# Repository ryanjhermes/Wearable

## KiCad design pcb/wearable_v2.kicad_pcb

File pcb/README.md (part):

# pcb — Wearable V2 schematic

KiCad project for the custom ESP32-C3 fab PCB. Open `wearable_v2.kicad_pro` in KiCad 10.

**This is the single living status document for the PCB. There are no dated handoff files.**
Read `## Current state`, `## Verified log` and `## Next actions` below; read the rest only if the
task needs it. `parts/V2_BOM.md` owns part rationale and approval status;
`bom_from_schematic.csv` owns reference designators and quantities.

**Update discipline:** documentation follows saved artifact changes; it does not predict them.
After changing and saving an artifact, run the required verification and immediately update this
file with the observed result and truthful next action. Never defer that update to the end of a
session.

## SETTLED — do not re-verify, do not re-open

Everything in this section is closed. A fresh agent must **not** re-run these checks, re-search these
parts, or re-litigate these decisions. Re-open an item only if the user asks, or if a design object it
depends on actually changes — and say which object changed before you do.

**Design checks — all pass, all current as of 2026-09-18.** The last design change was R10
270k -> 249k on 2026-09-18; ERC, DRC, schematic parity and `analyze_pcb.py` were all re-run after it
and returned results identical to the accepted 2026-09-17 baseline.

| Check | Accepted result | Do not re-run unless |
|---|---|---|
| `sch erc` | 2 violations = the 2 known `pin_to_pin` warnings | the schematic changes |
| `pcb drc` | 5 violations = the known-acceptable set, 0 unconnected | the board changes |
| `pcb drc --schematic-parity` | 0 parity issues, 0 unconnected | either design file changes |
| `analyze_pcb.py` | 51 findings: 2 error / 18 warning / 31 info, all reviewed and accepted | the board changes |
| Visual route + 3D review | Accepted for the first prototype | the board changes |
| CAD mechanical review | PASS for fabrication-file preparation; enclosure rebuilt 2026-09-18 | the board outline or battery envelope changes |
| Fabrication artifact validation | 15/15 PASS | the BOM, board or exports change |

**KiCad F8 (Update PCB from Schematic): do not run it.** The netlist has not changed since parity
last returned 0. KiCad 10.0.5 reintroduces a stale U4 pad net in this project when F8 runs. The
2026-09-18 R10 change was applied by patching the value/MPN/LCSC property fields in both files
directly, precisely to avoid this.

**Battery — CLOSED, final, by user decision 2026-09-18.** The EEMB `LP502030-PCM` already in the
user's possession is the cell for v2. EEMB's own LP502030 specification states a 250 mA maximum
charge current, so the planned 100 mA (0.4 C) is inside rating. **Do not search for alternative
cells, do not price-compare, do not re-open the envelope or wire-count questions.** Alternatives
investigated on 2026-09-17/18 are recorded in the log below for history only.

**JLCPCB — the decisions below are made. Do not re-derive, re-search or re-price them.**

| Settled | Value |
|---|---|
| Service | Standard PCBA |
| Layers / thickness | 4 layers, 1.0 mm |
| Panelization | Panel by JLCPCB, 5 mm process rails |
| Fiducials | Factory-added on the panel. **Do not add local board fiducials** unless JLCPCB actually rejects this workflow |
| Assembly sides | Top and bottom (45 top / 6 bottom) |
| Excluded from placement | BT1 and TP1-TP12 |
| R10 assembly class | `C11425` is Extended. So was the outgoing `C25770`. **No Basic 0402 1% part exists at either value** — checked 2026-09-18, does not need rechecking |
| Substitutions | Not acceptable for regulators, MOSFETs or connectors |
| Gerber/drill ZIP | Current and correct. R10's value lives only on F.Fab, which is not in the gerber set, so the 2026-09-18 change did not alter it |

**What genuinely still requires the live JLCPCB cart — once, not repeatedly.** These are not
desk-checkable and no amount of re-reading this repo will close them. They are the *only* JLCPCB work
left: confirm 4-layer/1.0 mm availability; run the cart's DFM; confirm the factory rails, fiducials
and tooling holes serve both assembly sides; read current stock, lifecycle, assembly class and price;
and eyeball the BOM/CPL overlay, especially J1, U1, U6, U7, U8, U10 and R10. Record the result once,
in the log below, and then treat it as settled too.

**Nothing here is fabrication approval.** Layout complete, checks clean, and artifacts validated are
all separate from reviewed, and all separate from ordered. No order is authorized.

## Current state — 2026-09-18

**The design is complete, internally consistent and fully verified on desk. It has never been built,
measured or ordered.**

*Schematic.* Captured, ERC-clean (2 understood warnings), frozen. One user-approved change since the
2026-09-16 freeze: R10 270k -> 249k on 2026-09-18, a value/MPN/LCSC change only — the netlist is
untouched.

*Layout.* 662 segments, 53 vias, 4 layers. Both inner GND zones filled and saved; In1.Cu carries no
traces and In2.Cu only the approved four 3V3 and two VSYS segments. Project-aware DRC without
refilling gives the 5 known-acceptable warnings, 0 unconnected items and 0 footprint errors; parity
gives 0 issues. `analyze_pcb.py` gives 51 reviewed and accepted findings. Route reviewed visually and
in 3D and accepted for the first prototype.

*Enclosure.* Rebuilt on 2026-09-18 after three structural defects were found in the 2026-09-17/18
geometry (see the log). The board is now mechanically captured: it sits on a 1.25 mm perimeter ledge
in the tray with 1.00 mm of bearing, is held down by full-length lid blocks on both long edges with a
0.05 mm nominal gap, and has 0.25 mm of lateral slop per side instead of 0.50. The halves join on a
continuous 2.445 mm lap joint whose four snap fingers are rooted in the lid wall over their full
6.0 x 0.7 mm section. Closed exterior is now **27.7 x 49.7 x 12.75 mm**. CAD review passes with zero
modeled hard collisions, 2.1 mm battery-to-antenna clearance, a single-piece USB mouth, separate
MAX30101 optical-gasket and TMP117 soft-thermal-pad volumes, and an unobstructed SHT40 vent.

*Power.* Desk power/thermal analysis and an ngspice simulation of the 4V7 boost are complete and give
a conditional pass. The worst-case 4V7 low corner is 4.770 V against the MAX30101's 4.5 V green
minimum, and a green LED pulse moves the rail only 4 mV, so boost dynamics are not a risk. **Two
firmware constraints carry into bring-up: cap BLE TX at 0 dBm, and hold `PPG_PWR_EN` low until 1V8 is
up.** The 3.45 V deep-sleep threshold is provisional pending a measured cell-sag figure.

*Battery.* **Closed and final.** EEMB LP502030-PCM already in hand; its 250 mA maximum charge rating
covers the planned 100 mA. Not to be re-sourced.

*Fabrication package.* `pcb/fabrication/jlcpcb_standard_pcba/` — gerbers, separate PTH/NPTH drills,
the authoritative 25-line/51-part BOM, 45-part top CPL, 6-part bottom CPL, PCB STEP and assembly
review artifacts. Regenerated after the R10 change; `artifact_validation.json` is 15/15 PASS.

*What is left.* Three things, all of which need hardware or the live cart, none of which can be
closed by further desk work: **the JLCPCB cart pass, printing and fit-testing the enclosure, and
bench-validating the rails on the first article.** See the SETTLED section above for what must not be
re-checked, and `## Verification NOT done` for the full list of what genuinely remains.

**Not bench-validated. Not peer-reviewed by a second person. Not approved for fabrication. No order
is authorized.**

## Verified log — append-only

Rows are chronological and **never edited or deleted**, so superseded rows remain visible. Two rows
below are superseded and must not be acted on: the `enclosure` row marked **BLOCKED** (superseded the
same day by the passing CAD mechanical review) and the `battery` row reporting a three-conductor
30 x 20 x 4 mm cell (superseded by the confirmed EEMB `LP502030-PCM` evidence, then closed entirely on
2026-09-18). Where a row conflicts with the SETTLED section or Current state above, those win.

Append one row per accepted check. Never edit or delete a row except to remove obsolete workflow
metadata such as revision fingerprints. A superseded result remains as historical evidence.

| Date | Artifact | Check | Result |
|---|---|---|---|
| 2026-09-16 | schematic | `kicad-cli sch erc` | 0 errors, 2 understood U9 strap warnings |
| 2026-09-16 | schematic | Hand netlist review, net by net | 3 silent opens found and fixed; no others |
| 2026-09-16 | schematic | BOM reconcile vs `parts/V2_BOM.md` | 25 lines / 51 populated, every qty matches |
| 2026-09-16 | schematic | IC pinouts vs local datasheets | 12/12 pin maps, **0 errors** |
| 2026-09-16 | schematic | Footprint courtyards | all 16 enclose their own pads |
| 2026-09-16 | schematic | JLCPCB assembly library, 25 lines | all present, `source: shop`, non-zero stock. **Stock drifts — recheck only at cart time** |
| 2026-09-17 | schematic | Independent electrical review against the exported netlist | **no new topology defect**; load share, USB-C, CC, ESD, straps, NCs all correct |
| 2026-09-17 | PCB | `pcb drc --schematic-parity` | **0 parity issues, 0 footprint errors** |
| 2026-09-17 | PCB | `pcb drc` clearance / edge | 0 errors |
| 2026-09-17 | PCB | Unconnected items | **9 remaining** (listed under `## Routing`) |
| 2026-09-17 | PCB | Courtyard overlap, all 64 footprints | 0 overlaps, all inside the outline |
| 2026-09-17 | PCB | Cell body vs `ANTENNA_KEEPOUT_U1` | **passes with 2.1 mm clearance** |
| 2026-09-17 | PCB | Silkscreen warnings | 2 remain, both J1 footprint outline at the intentional connector-mouth overhang |
| 2026-09-17 | PCB | Net-island analysis of the 9 open items (union-find over segments/vias/pads) | Confirms exactly 9. **VSYS is split into two islands**: `D1.1`+`Q1.2` vs everything downstream (`U4.1`, `U4.3`, `C3.1`, `C7.1`, `L1.1`, `TP5.1`). `/SW_PPG` has **zero** copper. All four U10 pads have zero copper |
| 2026-09-17 | PCB | `/SW_PPG` routed by direct file edit, U6.5 -> L1.2, F.Cu 0.4 mm | `pcb drc`: **8 unconnected (was 9), 6 violations identical to the known-acceptable set** |
| 2026-09-17 | PCB | Rule-area audit | **Three rule areas exist, not two.** An unnamed F.Cu `tracks not_allowed` area covers U10 (see `## Rule areas`) |
| 2026-09-17 | PCB | Item 7 `VSYS` -> U6.6 routed: F.Cu stub, via `(79.1375, 120.9)`, B.Cu to the VSYS diagonal | `pcb drc`: no new violation |
| 2026-09-17 | PCB | Item 4 `GND` U10.4 -> trunk at `(72.25, 142.1983)`, 0.25 mm through the notch then 0.4 mm | `pcb drc`: no new violation |
| 2026-09-17 | PCB | Full `pcb drc` after the above | **6 unconnected (from 9), 6 violations identical to the known-acceptable set** |
| 2026-09-17 | PCB | Item 3 `C10.2` GND attempted and **reverted** | Shorts `/BAT_SENSE`; C10 is walled in on F.Cu by R7 + the `/BAT_SENSE` diagonal and on B.Cu by the 3V3 run at y 114.4336. **Defer to the In1.Cu GND plane** |
| 2026-09-17 | PCB | Grid maze-route feasibility sweep of the 5 open items, F.Cu/B.Cu only (0.05 mm grid, exact clearance raster, all three rule areas enforced) | Items 9, 1, 2 routable. **Item 6 VSYS has no direct corridor** — best F/B path is 46.7 mm around the west board edge. **Item 5 `/SCL` has no path at all** |
| 2026-09-17 | PCB | Same sweep with `In2.Cu` allowed as a routing layer | Item 6 drops 46.7 mm -> **15.96 mm, 2 vias**; item 2 drops 20.8 mm -> 12.5 mm. **Item 5 is unaffected** — its blocker is via placement, not layer count |
| 2026-09-17 | PCB | Cause analysis of the item 5 `/SCL` blockage | U10.2 is boxed by the `BT1.1` pad + the F.Cu 3V3 feed at x 68.9307 (west), U10.1's pad (north), C20 + GND (south), the F.Cu notch keepout (east). `SHT40_U10_NO_COPPER` forbids a via anywhere it could reach. **Only opens if the 3V3 -> C20.1 feed is ripped up and rerouted** |
| 2026-09-17 | PCB | Item 1 `3V3` -> U10.3, and the logged "unresolved" C20 question | **Resolved: no B.Cu detour and no moving C20 needed.** 1.59 mm, 0 vias, all F.Cu: east through U10.3's notch, south around the keepout, west to C20.1 |
| 2026-09-17 | PCB | **Item 6 `VSYS` trunk routed on In2.Cu** — F.Cu out of `D1.1`, via `(64.4, 137.3)`, In2.Cu diagonal to `(71.4, 130.3)` then east to `(76.9, 130.3)`, via up to `U4.3`. 15.96 mm, 0.4 mm | `pcb drc`: 5 unconnected (from 6), no new violation |
| 2026-09-17 | PCB | **Item 9 `/PPG_PWR_EN` routed**, U6.4 -> via `(78.7, 123.05)` -> B.Cu -> the dangling via at `(72.965, 115.1131)`. 16.8 mm, 0.2 mm | `pcb drc`: 4 unconnected. **Also cleared the `via_dangling` warning** — that via is now a real connection, closing next-action 2 |
| 2026-09-17 | PCB | 3V3 feed to C20.1 **ripped up** (2 F.Cu segments at x 68.9307) per the 2026-09-17 user decision, and re-fed C20.1 from the existing via `(68.9307, 138.638)` down In2.Cu at x 69.4. 5.20 mm, 1 via (was 15.58 mm / 3 vias on F/B) | Opens the 0.62 mm western channel that item 5 needs |
| 2026-09-17 | PCB | **Items 5 `/SCL`, 2 `/SDA`, 1 `3V3` routed to U10** — all three escape laterally through their own 0.3 mm notch at exactly the pad centreline, then leave the corner. `/SCL` 22.9 mm / 3 vias, `/SDA` 24.5 mm / 3 vias, `3V3` 2.1 mm / 0 vias | `pcb drc`: **1 unconnected** — item 3 only |
| 2026-09-17 | PCB | Escape-geometry cleanup: 3 `connection_width` necks (0.040 / 0.115 / 0.128 mm) and 1 `hole_clearance` violation against BT1's NPTH at `(67.4, 139.6)` | All 4 fixed. Root cause: a track that only *touches* a pad or via edge is tangent, not connected |
| 2026-09-17 | PCB | `pcb drc` full, in-project | **5 violations = exactly the known-acceptable set, 1 unconnected (item 3, deferred to the pour), 0 footprint errors** |
| 2026-09-17 | PCB | `pcb drc --schematic-parity` | **0 parity issues, 0 footprint errors** |
| 2026-09-17 | PCB | In2.Cu trace inventory | Exactly 2 nets: `VSYS` trunk (2 segments, 0.4 mm) and the `3V3` C20 feed (4 segments, 0.3 mm, ~3.9 mm long). **In1.Cu is still completely empty** |
| 2026-09-17 | PCB | Project-aware `pcb drc` after interactive U10 move + plane-pour attempt | **REGRESSION: 24 violations and 75 unconnected items.** Includes 2 zones forbidden by `SHT40_U10_NO_COPPER`, 11 clearance, 4 hole-clearance and 1 connection-width issue; 6 are the previously known silk/library warnings. The GND zones do not yet provide a valid connectivity result |
| 2026-09-17 | PCB | `pcb drc --schematic-parity` | **0 schematic parity issues**; the temporary stale U4 VIN net seen in KiCad history is not present in this saved state |
| 2026-09-17 | PCB | Exact recovery after the interactive regression | **RESTORED byte-for-byte from the agent scratch artifact** with PCB Editor closed: 661 segments, 52 vias, 3 rule areas and no copper-pour zones. Existing applicable checks stood and were not redundantly rerun |
| 2026-09-17 | project settings | Restore text/graphic defaults after accidental 0.1 mm horizontal-size edits | `wearable_v2.kicad_pro` matches the committed defaults again: Fab/Other 1.0 x 1.0 mm, 0.15 mm stroke; Silk 1.0 x 1.0 mm, 0.10 mm stroke |
| 2026-09-17 | PCB | Project-aware `pcb drc` after KiCad re-save of the recovered route | **5 violations = exactly the known-acceptable set, 1 unconnected (`C10.2` GND, deferred to the pour), 0 footprint errors** |
| 2026-09-17 | PCB | `pcb drc --schematic-parity` | **0 schematic parity issues, 0 footprint errors** |
| 2026-09-17 | PCB | C10 ground-plane feasibility correction + In1/In2 GND-zone definitions | Added a 0.2 mm `C10.2` stub to a GND through-via at `(64.78, 113.20)`. This corrects the earlier assumption that an inner plane could directly contact a top-side SMD pad; it cannot do so without a via |
| 2026-09-17 | PCB | Project-aware `pcb drc --refill-zones` and parity check (in-memory refill; fills not saved) | **5 violations = exactly the known-acceptable set, 0 unconnected items, 0 footprint errors, 0 schematic parity issues** |
| 2026-09-17 | PCB | Visual route review from F.Cu/B.Cu/In2.Cu plots and top/bottom 3D renders | Accepted for the first prototype. Long SHT40 SDA/SCL and PPG enable runs are low-speed/static; boost SW is 3.41 mm and FB is 3.98 mm; MAX30101 bypass parts are adjacent on B.Cu. USB is the weakest-looking route, but end-to-end D+/D- lengths are approximately 67.1/69.6 mm and the MCU-side resistor stubs are 2.59/2.91 mm. Preserve as a known first-spin signal-integrity risk rather than churn DRC-clean copper cosmetically |
| 2026-09-17 | PCB | Saved zone-fill presence check after the user pressed `B` and saved | 2 filled polygons present: one for `GND_PLANE_In1`, one for `GND_PLANE_In2`; final no-refill DRC waits until PCB Editor is closed |
| 2026-09-17 | PCB | Final project-aware `pcb drc` against the saved fills, without refilling | **5 violations = exactly the known-acceptable set, 0 unconnected items, 0 footprint errors** |
| 2026-09-17 | PCB | Final `pcb drc --schematic-parity` against the saved fills | **0 schematic parity issues, 0 footprint errors** |
| 2026-09-17 | PCB | Saved inner-layer inventory | 2 filled polygons; In1.Cu has 0 trace segments; In2.Cu has exactly 6 segments: 4 on 3V3 and 2 on VSYS |
| 2026-09-17 | PCB | Final `kicad-happy` `analyze_pcb.py` review | Analyzer completed successfully: 662 segments, 53 vias, 4 copper layers, 0 unrouted nets. Reviewed all 51 raw findings (2 error / 18 warning / 31 info). U10-inside-keepout is the intentional sensor copper keepout; U1 pad-49 thermal-via repeats are one module-land heuristic repeated eight times; narrow low-current signals, 0402 thermal-asymmetry notices, 11/61 test-net coverage, 3 GND stitching vias, J1/U1 edge placement and C7-C11 edge-clearance warnings are accepted first-prototype risks. Existing U1/U6/U8 footprint overrides and J1 silk-edge warnings remain intentional. |
| 2026-09-17 | PCB assembly | JLCPCB fiducial workflow decision | Use **Standard PCBA with Panel by JLCPCB / 5 mm edge rails** and factory-added panel fiducials/tooling holes; do not consume this 24 x 46 mm board with local fiducials. Confirm the generated rails/fiducials on both assembly sides during cart DFM review. |
| 2026-09-17 | enclosure | Final mechanical-review gate | **BLOCKED, not accepted:** `enclosure/` has no enclosure model or opening geometry, and the exact protected battery dimensions/wire exit are unresolved. USB-C opening alignment, MAX30101/TMP117 skin-opening contact and SHT40 vent clearance cannot be confirmed. The nominal 30 x 20 mm cell-to-antenna clearance remains the previously accepted 2.1 mm PCB-layout result, not an enclosure/battery fit check. No fabrication outputs generated. |
| 2026-09-17 | battery | Selected-cell identity and reported envelope | User selected the already-owned protected 402030, 3.7 V, 250 mAh three-conductor cell and reported a 30 x 20 x 4 mm maximum envelope. No substitute sourcing or circuit redesign. Mechanical integration remains blocked pending bulge/envelope confirmation, wire-exit evidence, polarity, third-conductor identification and 100 mA charge permission. |
| 2026-09-17 | battery | Selected-cell product evidence | User supplied the exact listing and label photo for EEMB `LP502030-PCM` (ASIN `B08VRZTHDL`): protected 3.7 V, 250 mAh, 32 x 20.5 x 5.3 mm, 5 g. The pictured selected pack has two wires exiting beside the PCM, not three; its label explicitly marks red positive and black negative. This supersedes the earlier reported envelope and three-wire concern. The listing does not establish a charge-current rating, so 100 mA permission remains open. |
| 2026-09-17 | enclosure + populated PCB STEP | Parametric CAD mechanical review | **PASS for fabrication-file preparation; physical fit still open.** Generated 28 x 50 x 12.4 mm enclosure around the populated PCB STEP and selected battery envelope. CAD reports 0.0 mm^3 hard-shell/PCB, shell/battery, cradle/PCB, battery/PCB and wire-path/PCB intersections; battery-to-antenna 2.1 mm, battery-to-roof 0.35 mm, USB side/vertical opening clearance 0.53/0.70 mm. MAX30101 uses a cleared opaque-gasket volume, TMP117 a zero-interference soft thermal-pad volume, and SHT40 a direct exterior vent. Evidence: `enclosure/generated/mechanical_review/mechanical_review.json`, STEP/STL assembly parts and isometric previews. J1/U7/U10 use documented conservative envelope surrogates because their local KiCad 3D models were unavailable. |
| 2026-09-17 | fabrication package | Gerber/drill/BOM/CPL/STEP export and local artifact validation | **PASS locally; cart gates remain open.** `pcb/fabrication/jlcpcb_standard_pcba/` contains upload ZIPs, 4 copper layers, paste/mask/silkscreen, separate PTH/NPTH drill files, assembly PDFs/renders and PCB STEP. Outline centerline is exactly 24 x 46 mm. Gerber viewer top/bottom review shows aligned copper, mask, drill and outline. BOM is 25 lines/51 parts; CPL is the identical 51 references split 45 top/6 bottom. BT1 and TP1–TP12 are excluded. J1/U1/U6/U10 top 0 degrees and U7/U8 bottom 180 degrees match KiCad. Evidence: `artifact_validation.json`. Four-layer/1.0 mm live availability, factory 5 mm rails/fiducials/tooling for both sides, DFM, current sourcing and price must still be confirmed in the JLCPCB cart. |
| 2026-09-17 | power tree | Desk power/thermal margin analysis — gate 3 (analysis only, no bench) | **CONDITIONAL PASS with two firmware constraints and one open corner. No design file changed.** 3V3 budget from datasheet peaks: 17 mA sensing, 90 mA BLE RX, 174 mA BLE TX at 0 dBm, 344 mA BLE TX at 20 dBm (ESP32-C3-MINI-1 p22 + 4 mA for the XC6206 branch, SHT40, TMP117 and two 4.7 k I2C pull-ups). ME6211 dropout linear-extrapolated from its only two published typical points (120 mV/100 mA, 260 mV/200 mA, me6211/datasheet.pdf p8): ~224 mV at 174 mA and ~462 mV at 344 mA. At a 3.45 V cell with 0.085 Ohm Q1 max plus an **assumed** 0.25 Ohm cell+PCM ESR, 3V3 holds 3.17 V at 0 dBm TX but falls to 2.87 V at 20 dBm TX — below the module's 3.0 V VDD33 minimum (esp32-c3-mini-1/datasheet.pdf p21). USB-powered LDO dissipation is 226 mW at 0 dBm and 447 mW at 20 dBm against a 300 mW SOT-23 rating (me6211/datasheet.pdf p5). 4V7 rail: PWM divider worst-case corner is 4.538 V, and 50 nA max FB leakage across R9 = 1 MOhm can subtract a further 50 mV, giving **4.488 V — under the 4.5 V green VLED+ minimum** (tps61099/datasheet.pdf p5; max30101/datasheet.pdf p2). Light-load PFM sits at ~4.845 V, safely under the 5.6 V OVP minimum. 4V7 COUT is C8+C9+C15+C16 = 24.8 uF nominal, ~13.9 uF at a pessimistic 50% DC-bias derate, still inside TI's 10-100 uF recommendation. Hysteretic charge packet is 0.135 uC, so PFM ripple is ~8.5 mV and a 51 mA green pulse needs ~156 switch pulses (~152 us) within its 411 us window; capacitor-only sag is ~10 mV at 3 us and ~32 mV at 10 us of loop delay. L1 peak is ~247 mA against 1.5 A saturation and a 0.8 A minimum switch limit. TP4054 at 100 mA dissipates ~130 mW. Evidence: local datasheets as cited. **Not measured. TPS61099 publishes no switching-frequency, ripple, start-up or numeric transient spec, ME6211 publishes no theta-JA, no TJ(max) and no dropout maximum, MAKK2016 has no local datasheet, and the cell+PCM ESR is assumed, not sourced.** |
| 2026-09-17 | power tree | Boost topology confirmation from the saved PCB netlist | TPS61099 input is on `VSYS` (L1 pad 1, U6 pad 6), not `3V3`, so green-LED energy does not pass through the ME6211. MAX30101 VLED+ pads 9/10 are on `4V7`, VDD pad 11 on `1V8`. The 1V8 branch is XC6206 from `3V3` feeding MAX30101 VDD and the LSM6DS3TR-C, ~2 mA worst case. |
| 2026-09-18 | 4V7 rail | ngspice behavioral simulation of the TPS61099 boost — gate 3 dynamic half | **Dynamic behaviour PASSES with wide margin; the DC tolerance stack is the only failure mode, and it confirms the R10 finding.** Netlist `pcb/analysis/tps61099_4v7_boost.cir`, ngspice 47, no design file changed. Model is behavioral, not TI silicon: hysteretic peak-current control with the datasheet's 350 mA fixed inductor ripple, 300/350 mOhm Rds(on), 1.03 V PFM reference, MAKK2016 2.2 uH/0.16 Ohm, the real C7/C3/C8/C9/C15/C16 network DC-bias derated, 2 nH of bulk-to-sensor trace, and the MAX30101 51 mA / 411 us / 100 sps green pulse. Light-load PFM sits at 4.830-4.869 V, agreeing with the 4.845 V hand calculation. **The LED pulse pulls the rail down only 4 mV** (to 4.826 V) — the converter tracks it easily, so the idle-to-pulse transient is not a risk. Peak inductor current 363-366 mA against 1.5 A saturation and the 0.8 A minimum switch limit. VIN 3.5 / 3.7 / 4.2 V changes the rail by under 2 mV; no down-mode entry (threshold is VIN > 4.78 V). Raising assumed FB-node capacitance from 5 pF to 20 pF costs only 15 mV of ripple, which retires the concern that the 1 MOhm divider impedance would slow the loop dangerously. Worst-case corner with VREF at its 0.98 V PWM minimum, 1% resistor endpoints and 50 nA of FB leakage injected: **4.470 V with R10 = 270k (30 mV under the 4.5 V green minimum) and 4.770 V with R10 = 249k (270 mV above it)**, within 20 mV of the hand calculation. **Model-dependent caveats: the 5 mV burst-comparator hysteresis is assumed, not published; TI publishes no min/max for the PFM reference, no switching-frequency, ripple or start-up spec; start-up, temperature and MAX30101 pin-level waveforms were not simulated. This is a desk model, not a measurement.** |
| 2026-09-18 | battery | EEMB LP502030 charge-current evidence found — gate 1 substantially closed | EEMB's own LP502030 cell specification (ZJQM-RD-SPC-H2305, 2022-10-25, linked from eemb.com/product-130, accessed 2026-09-18) states **maximum charge current 250 mA, 1.0C5A (CC&CV)**. The planned TP4054 charge current of 100 mA is 0.4 C, inside that rating. **This supersedes the earlier conclusion that no charge rating existed for the selected cell.** Residual gap: that document is the bare-cell revision and gives dimensions as <=31 x 20.5 x 5.3 mm with no PCM section, so it does not itself document the -PCM pack's protection-circuit current limits or finished pack length. Backup candidate if a distributor-sourced cell with pack-level documentation is preferred: Cellevia ACCU-LP502030/CL, 250 mAh, 30 +/-0.4 x 20 +/-0.4 x 5.0 +/-0.2 mm pack, two 26AWG wires, standard charge 125 mA / rapid charge 250 mA, sold by TME; its price, stock and US availability are unverified. Jauch LP502030JH+PCM was rejected on envelope: DigiKey states 32.0 x 21.0 x 5.4 mm, over both the 20.5 mm width and 5.3 mm thickness limits. |
| 2026-09-18 | enclosure | Separate top/bottom snap-fit revision | **PASS in CAD; physical snap test open.** Rebuilt the enclosure as two separate one-solid printable parts while retaining the 28 x 50 x 12.4 mm closed exterior. The lid has four 4.0 x 0.45 x 2.3 mm wall-mounted cantilever tabs with 0.20 mm hooks; the tray has matching concealed catches with 0.125 mm clearance per tab face. Fixed the earlier disconnected battery rails by bridging them into the lid. Regenerated STEP/STL/assembly/review artifacts. CAD reports 0.0 mm^3 assembled top/bottom overlap and 0.0 mm^3 snap-tab/PCB intersection; all prior mechanical checks still pass. First print should use PETG or nylon and validate/tune latch clearance before release. |
| 2026-09-18 | battery | **Battery selection CLOSED by user decision — final, not to be reopened** | The EEMB `LP502030-PCM` already in the user's possession is the battery for v2. Charge-current permission is satisfied by EEMB's own LP502030 specification (250 mA maximum, 1.0C5A CC&CV), against which the TP4054's 100 mA is 0.4 C. Alternative cells investigated on 2026-09-17/18 are recorded above for history only; **do not source a substitute and do not reopen this question.** Residual documentation gap, explicitly accepted by the user: the EEMB document is the bare-cell revision and does not specify the -PCM pack's protection trip current or finished pack length. |
| 2026-09-18 | schematic + PCB | **R10 270k -> 249k — user-approved schematic change, implemented and verified** | R10 value, MPN (`0402WGF2703TCE` -> `0402WGF2493TCE`) and LCSC code (`C25770` -> `C11425`) changed in both `wearable_v2.kicad_sch` and the R10 footprint properties in `wearable_v2.kicad_pcb`. Diff against a pre-change backup is **exactly 3 lines in each file**; no copper, net, footprint or position changed. **KiCad F8 was deliberately NOT rerun** — the netlist is unchanged, so the documented KiCad 10.0.5 stale-U4-pad hazard was avoided by patching the two files' property fields directly. KiCad PCB Editor was confirmed closed and no `.lck` files were present. Verification after the change: **ERC 2 violations = the 2 known `pin_to_pin` warnings; `pcb drc` 5 violations = exactly the known-acceptable set (2 J1 silk-edge, 3 library overrides for U1/U6/U8) with 0 unconnected items; `pcb drc --schematic-parity` 0 parity issues, 0 unconnected; `analyze_pcb.py` 51 findings / 2 error / 18 warning / 31 info — byte-identical severity split to the accepted 2026-09-17 run.** Zero regressions. Nominal 4V7 rail moves from 4.704 V to 5.016 V; worst-case low corner from 4.470 V to 4.770 V. |
| 2026-09-18 | fabrication package | Regenerated after the R10 change and revalidated | `pcb/bom_from_schematic.csv` R10 row updated; top/bottom raw position files and both assembly PDFs re-exported from the changed board; `build_and_validate.py` rerun. `artifact_validation.json` = **PASS on all 15 checks** (24 x 46 mm outline, 4 copper layers, 1.0 mm, 25 BOM lines / 51 parts, 45 top / 6 bottom CPL, BT1 and TP1-TP12 excluded, critical orientations match). **The gerber/drill ZIP is unchanged and did not need regenerating** — R10's value lives only on F.Fab, which is not part of the exported gerber set. `wearable_v2_pcba_bom_cpl.zip` was found stale after the rebuild and was regenerated; the zipped BOM now reads `249k,R10,...,C11425`. No stale `270k`/`C25770`/`2703TCE` string remains anywhere under `pcb/fabrication/`. |
| 2026-09-18 | documentation sync | Stale `270k` / `C25770` references cleared across the repo, and re-verified | Updated: the schematic's on-sheet annotation text (now `VOUT = 1.0 V x (1M + 249k) / 249k = 5.016 V nominal.`), `parts/tps61099/README.md` required-externals table, the passive inventory line in this file, and the JLCPCB parts table in `parts/V2_BOM.md`. **JLCPCB assembly class confirmed unchanged: C11425 (249k) and C25770 (270k) are both Extended — no Basic 0402 1% part exists at either value**, so the R10 change adds no assembly-class burden. C11425 stock 44,965 at approximately $0.0005/ea (jlcsearch, accessed 2026-09-18); treat stock, lifecycle and price as cart-verified only. Re-verified after the annotation edit: **ERC 2 violations (the known pair), `pcb drc` 5 violations with 0 unconnected, parity 0 issues.** `docs/DESIGN_HISTORY.md` deliberately still records C25770 — it is the historical rationale document and is not authoritative. |
| 2026-09-18 | enclosure | **Structural rebuild — three defects found and fixed in the snap-fit revision** | **PASS in CAD; physical print and fit test still open.** Audit of the 2026-09-18 snap-fit geometry found three defects that would have made a printed part useless. (1) Each of the four snap tabs was joined to the lid over only **0.10 mm of height, 0.18 mm^3** of weld: the tab spanned z -2.05..+0.25 while the lid wall began at z +0.15, so a 2.2 mm cantilever hung from a sliver thinner than one FDM layer. (2) **The PCB was not retained at all** — the tray cavity was a plain 25 x 47 x 1.85 mm pocket with no ledge, standoff or hold-down, leaving the board floating with 0.50 mm of lateral slop and 1.05 mm of vertical travel. (3) The parting line at z +0.15 ran 0.195 mm *below* the board's top face, so the tray rim could never capture the board edge. `enclosure/generate_enclosure.py` was rewritten around a measured board datum (STEP bodies: board face -0.085..+0.995, top-side bodies from +0.995, lowest bottom-side body -0.905; shifted by -0.65). New structure: parting plane on the board's top face; tray carries a 1.25 mm perimeter ledge (1.00 mm bearing) plus four blind snap catches; lid carries a continuous 0.70 mm lap skirt 2.445 mm deep, four 6.0 x 0.70 mm snap fingers rooted over their full section (**2.10 mm^3**, 11.7x the old weld) with 0.20 mm hooks, full-length PCB hold-down blocks on both long edges (2.30 mm west / 1.00 mm east overlap, 0.05 mm gap), battery shelves bearing 0.55 mm west and 0.70 mm east, and a 0.60 mm battery end stop immediately north of the cell so it cannot drift over the trace antenna. Footprint tightened to **27.7 x 49.7 mm** (1.6 mm wall, 0.25 mm slop per side); height is **12.75 mm**, up 0.35 mm, to buy lap-joint depth and a 0.72 mm floor under the joint groove. Peak snap bending strain is **3.51%** by eps = 1.5*t*delta/L^2, inside PETG's short-term allowable; PLA is unsuitable. Verification: `enclosure/generate_enclosure.py` run under `.venv` (CadQuery 2.8.0, installed this session), exit 0, **24/24 checks pass**; all 12 collision volumes 0.0000 mm^3 including hard shell vs populated PCB, shell vs battery and assembled top vs bottom. Independent STL check: both parts are **1 connected component with 0 non-manifold edges**. Evidence: `enclosure/generated/mechanical_review/mechanical_review.json`, regenerated STEP/STL/SVG. **This supersedes the 2026-09-17 and earlier 2026-09-18 enclosure rows.** Two defects the rebuild does not remove and the first print must check: the battery end stop bridges 13.2 mm over the ESP32-C3-MINI-1 when the lid prints roof-down, and the USB-C mouth is sized to the receptacle envelope, not to a specific cable overmold. |
| 2026-09-18 | documentation | Full documentation-consistency pass and checkpoint | Added the `## SETTLED — do not re-verify, do not re-open` section at the top of this file, recording the closed design checks, the closed battery decision and the settled JLCPCB settings, so a fresh agent does not re-run or re-search them. Rewrote `## Current state` (it had become a lumpy accretion of edits), replaced `## Next actions` with three live hardware/cart items plus a compressed completed-work table, and rewrote `## Verification NOT done`, whose three entries were all stale — the electrical review, power-budget work and routing they listed as outstanding are done. Noted in the log preamble which two rows are superseded, since the log is append-only and both still read as live blockers. Synced `CLAUDE.md` (layout is complete; open questions rewritten; cell recorded as final), `parts/V2_BOM.md` (status section, gate 4, JLCPCB parts table), `parts/V2_HARDWARE_AUDIT.md` (finding 3 marked resolved), `enclosure/README.md` (charge-current item closed) and the fabrication package README. **No design file was touched in this pass, so ERC, DRC, parity and the analyzer were deliberately not re-run** — their 2026-09-18 results stand. |

Known-acceptable warnings that must be **preserved**, not "fixed": the 2 J1 silk-to-edge warnings,
and 3 footprint-library mismatches (U1 project override; U6/U8 deliberate pad-7 overrides).

## Next actions — in order

**Nothing on this list can be closed from the keyboard.** All three remaining items need the live
JLCPCB cart, a 3D printer or a built board. If you are a fresh agent and you find yourself re-running
DRC or re-searching parts, stop and read the SETTLED section at the top of this file.

1. **JLCPCB cart pass — the only remaining JLCPCB work.** Upload
   `pcb/fabrication/jlcpcb_standard_pcba/wearable_v2_gerbers_drills.zip`,
   `assembly/jlcpcb_bom.csv`, `assembly/jlcpcb_top_cpl.csv` and `assembly/jlcpcb_bottom_cpl.csv`.
   Settings are already decided (Standard PCBA, 4 layers, 1.0 mm, Panel by JLCPCB, 5 mm rails — see
   SETTLED). Confirm in the cart: 4-layer/1.0 mm availability, the DFM result, that factory rails,
   fiducials and tooling holes serve **both** assembly sides, current stock/lifecycle/assembly
   class/price, and the BOM-CPL overlay for J1, U1, U6, U7, U8, U10 and R10. Reject similar
   substitutions for regulators, MOSFETs and connectors. Record the outcome once in the verified log.
2. **Print and fit-test the enclosure** with the real PCB, the EEMB cell, the optical gasket and the
   TMP117 thermal pad. CAD clearance is not tolerance validation. Geometry and evidence are under
   `enclosure/generated/mechanical_review/`. Print in PETG or nylon, not PLA. Specifically check the
   0.10 mm lap-joint clearance per face, the 0.20 mm snap-hook engagement, the 0.05 mm PCB hold-down
   gap, the 13.2 mm roof-down bridge over the ESP32 module, and that a real USB-C cable's overmold
   reaches the receptacle.
3. **Bench-validate the rails on the first article.** 3V3 under simultaneous BLE TX, flash write and
   PPG pulses at low battery and across cable insertion; 4V7 start-up, ripple and temperature
   behaviour measured at the MAX30101 VLED+ pins; ME6211 case temperature on USB; and LP502030-PCM
   terminal sag at 200 mA and 400 mA to replace the assumed 0.25 Ohm cell+PCM resistance and fix the
   provisional 3.45 V deep-sleep threshold.

**Carry into firmware bring-up** (the desk analysis depends on both): cap BLE TX power at 0 dBm, and
hold `PPG_PWR_EN` low until the 1V8 rail is established.

**Do not place an order or claim fabrication approval without explicit user authorization.**

### Completed — for the trail only, do not redo

| Done | What |
|---|---|
| 2026-09-17 | Recovered the exact PCB after the interactive regression; restored project text/graphic defaults |
| 2026-09-17 | Closed the 9 remaining connections, including the `C10.2` GND via to In1.Cu; removed the dangling `/PPG_PWR_EN` via |
| 2026-09-17 | Visual route review — accepted for the first prototype, with the long `/SDA`, `/SCL`, `/PPG_PWR_EN` runs and the USB D+/D- route preserved as known first-spin risks |
| 2026-09-17 | Silkscreen pass; references hidden, only the 2 intentional J1 connector-mouth edge warnings left |
| 2026-09-17 | Saved and verified both inner GND pours |
| 2026-09-17 | Final `kicad-happy` PCB analysis reviewed and accepted; JLCPCB panel/fiducial workflow decided |
| 2026-09-17 | Enclosure CAD mechanical review — PASS for fabrication-file preparation |
| 2026-09-17 | Generated and locally validated gerbers, drills, BOM, top+bottom CPL and PCB STEP |
| 2026-09-17/18 | Desk power/thermal margin analysis — conditional pass; produced the 0 dBm TX cap and the R10 finding |
| 2026-09-18 | ngspice simulation of the 4V7 boost — dynamics are not a risk; confirmed the DC corner |
| 2026-09-18 | **R10 270k -> 249k** implemented, verified (ERC/DRC/parity/analyzer all unchanged) and re-exported |
| 2026-09-18 | **Battery closed, final** — EEMB LP502030-PCM, 250 mA max charge rating covers the planned 100 mA |
| 2026-09-18 | Repo-wide documentation sync; stale `270k`/`C25770` references cleared |

## What is here

| File | Role |
|---|---|
| `wearable_v2.kicad_sch` | **The schematic. Authoritative from the moment you open it.** |
| `wearable_v2.kicad_pro` | Project file |
| `symbols/wearable_v2.kicad_sym` | Project symbols: the five parts with no stock-library equivalent |
| `pcb.pretty/` | Project footprints — **all three now present and verified** |
| `pcb.3dshapes/` | STEP models for the module and inductor (needed later for enclosure fit) |
| `bom_from_schematic.csv` | BOM generated from the schematic — 25 lines, 51 populated parts, with `Qty`/`MPN`/`LCSC` |
| `.kicad-happy.json` | Config for the `kicad-happy` analysis skills: supplier, design intent, rail voltages, suppressions |
| `datasheets/` | MPN-named symlinks into `parts/*/datasheet.pdf`, so the analyzers can verify pinouts |

### The bootstrap generators have been removed

`build.py` and its helpers (`schgen.py`, `libtool.py`, `sexp.py`, `mksym.py`, `gen_lib.py`) wrote
the first `.kicad_sch` and were deleted once it had been hand-edited. Re-running any of them
regenerates the schematic from scratch and discards every placement, wire and fix — and one of
their defects (never emitting `(junction ...)` items) had already cost a silent open on the 3.3 V
rail. They remain in git history if the provenance of the first draft is ever needed. **The
`.kicad_sch` is the only source of truth.**

### Part properties

Every BOM symbol carries both an `MPN` and an `LCSC` property. `MPN` was added 2026-09-16 — the
sourcing gate and the JLCPCB BOM/CPL export both key on it, and without it the analyzers refuse
to call any electrical finding "verified".

## Sheet layout

One A2 root sheet, seven dashed blocks. Inter-block nets use labels and power symbols rather than
long drawn wires, so blocks can be moved without re-routing.

| Block | Contents |
|---|---|
| A | USB-C receptacle, CC pulldowns, USBLC6 ESD array |
| B | TP4054 charger, AO3401A + SS14 load sharing, battery pads, battery-sense divider |
| C | ME6211 3.3 V and XC6206 1.8 V linear regulators |
| D | TPS61099 4.7 V boost for the green LED rail |
| E | ESP32-C3-MINI-1, EN reset RC, strapping pull-ups, USB series resistors, I2C pull-ups |
| F | MAX30101, TMP117, LSM6DS3TR-C, SHT40 on one I2C bus |
| G | Twelve bring-up test pads |

## Verification done

- **ERC: 0 errors, 2 warnings** (both understood, listed below). Was 5 warnings before
  the footprints landed on 2026-09-16.
- **Netlist reviewed by hand, net by net.** Two real defects were found and fixed during capture:
  - The LSM6DS3TR-C ground ties were routed across the SDA/SCL stubs, **shorting the whole I2C
    bus to ground**. Ties now route away from the bus pins.
  - `BAT+` existed as two separate nets (a power symbol and a local label), so **the cell was not
    connected to the charger**, and the AO3401A gate sat on its own net instead of VBUS, which
    would have left the load-share MOSFET permanently on. Both are now single nets.
- **BOM reconciles exactly against `parts/V2_BOM.md`: 51 populated components**, and every
  per-value quantity matches (100 nF x8, 1 uF x6, 4.7 uF x2, 10 uF x4, 22R x2, 4.7k x2, 5.1k x2,
  10k x5, 100k x2, 1M x3, 249k x1, 14 non-passives).
- **Pinouts checked against the local datasheets in `parts/`** for every IC.
- **A third silent open was found and fixed on 2026-09-16: U4 pin 1 (VIN) was on no net**, so the
  board had no 3.3 V rail at all. The wire T'd into the middle of the VSYS wire, and KiCad does
  not connect a mid-wire T without an explicit `(junction ...)` item — of which the generated
  schematic had **zero**. Two junctions were added. Every wire endpoint and symbol pin in the
  schematic was then swept for the same failure mode; **U4 VIN was the only instance.** Verified
  against `kicad-cli`'s own exported netlist, not a third-party parser: `VSYS` now carries
  `U4.1` and `U4.3`, and `unconnected-(U4-V_{IN}-Pad1)` is gone.

## Verification NOT done — do not treat this as reviewed

**Rewritten 2026-09-18.** The three items that used to sit here are resolved; see the SETTLED section
at the top of this file. For the record: the electrical topology review was accepted 2026-09-17;
power-budget, ME6211 dropout/thermal and TPS61099 rail margin were analysed on desk 2026-09-17/18 and
the boost was simulated in ngspice; routing is complete, poured, DRC-clean and visually accepted.

What remains genuinely unverified is **everything that needs physical hardware or the live cart.** Do
not attempt to close these by reading or re-analysing this repo:

1. **No bench measurement of anything.** Every power-rail number in this repo is a desk calculation
   or a behavioral simulation. Still needed on the first article: 3V3 under simultaneous BLE TX,
   flash write and PPG pulses at low battery and across cable insertion; 4V7 start-up, ripple and
   behaviour over temperature measured at the MAX30101 VLED+ pins; ME6211 case temperature on USB;
   and LP502030-PCM terminal sag at 200 mA and 400 mA, which replaces the assumed 0.25 Ohm cell+PCM
   resistance and confirms or moves the provisional 3.45 V deep-sleep threshold.
2. **No physical fit test.** The enclosure passes in CAD only. Print it and fit it with the real PCB,
   cell, optical gasket and TMP117 thermal pad before treating any tolerance as production-ready.
3. **No live JLCPCB cart pass.** Listed in the SETTLED section; it is the only remaining JLCPCB work.
4. **No peer electrical review by a second person.** The topology review was one author's pass.
5. **Wrist-PPG wavelength has never been measured.** This is a post-arrival firmware experiment
   (`archive/v1/src/max30102_raw_ir/`), not an ordering gate.

**Two firmware constraints must be carried into bring-up** or the analysis above does not hold: cap
BLE TX power at 0 dBm, and hold `PPG_PWR_EN` low until the 1V8 rail is established.

## Footprint audit — done 2026-09-16 (release gate #5)

Method: resolve all 16 distinct footprints to their `.kicad_mod`, extract real pad geometry, and
compare **pad-number → function** against the manufacturer datasheet pin table, and pad geometry
against the vendor land pattern where the datasheet contains one.

### Pin maps — 12 of 12 verified, zero errors

Every IC, connector and discrete was checked pad-by-pad against its datasheet pin table (not the
package name). **No pinout error was found.**

| Ref | Part | Datasheet pin table | Verdict |
|---|---|---|---|
| U2 | USBLC6-2SC6 | 1 I/O1, 2 GND, 3 I/O2, 4 I/O2, 5 VBUS, 6 I/O1 | ✅ hand-authored symbol matches; DM through 1→6, DP through 3→4 |
| U3 | TP4054 | 1 CHRG, 2 GND, 3 BAT, 4 VCC, 5 PROG | ✅ |
| U4 | ME6211C33M5G-N | 1 VIN, 2 VSS, 3 CE, 4 NC, 5 VOUT | ✅ CE tied to VSYS |
| U5 | XC6206P182MR | 1 VSS, 2 VOUT, 3 VIN | ✅ |
| U6 | TPS61099DRVR | 1 GND, 2 VOUT, 3 FB, 4 EN, 5 SW, 6 VIN, 7 PowerPAD→GND | ✅ incl. PowerPAD on GND as required |
| U7 | MAX30101EFD+T | 1 NC, 2 SCL, 3 SDA, 4 PGND, 5–8 NC, 9/10 VLED+, 11 VDD, 12 GND, 13 INT, 14 NC | ✅ |
| U8 | TMP117AIDRVR | 1 SCL, 2 GND, 3 ALERT, 4 ADD0, 5 V+, 6 SDA | ✅ ADD0→GND = 0x48 |
| U9 | LSM6DS3TR-C | 1 SDO/SA0, 2 SDx, 3 SCx, 4 INT1, 5 VDDIO, 6/7 GND, 8 VDD, 9 INT2, 10/11 NC, 12 CS, 13 SCL, 14 SDA | ✅ SA0→GND = **0x6A**; CS→3V3 = I2C mode |
| U10 | SHT40-AD1B-R3 | 1 SDA, 2 SCL, 3 VDD, 4 VSS | ✅ |
| Q1 | AO3401A | 1 G, 2 S, 3 D | ✅ G→VBUS, S→VSYS, D→BAT+ |
| D1 | SS14 | — | ✅ symbol pin 1 = K, `D_SMA` pad 1 is the cathode end (F.Fab bar + silk band both on the pad-1 side); K→VSYS, A→VBUS |
| L1 | MAKK2016T2R2M | non-polar | ✅ |

Two datasheet details worth re-reading before layout: LSM6DS3TR-C pins 10/11 are
*"leave electrically unconnected **and soldered to PCB**"* (the footprint has pads, so this is
satisfied), and both its VDD and VDDIO want their own 100 nF — which the BOM already fits.

### Geometry — courtyards

All 16 footprints have a courtyard that fully encloses their own pads. (This was the bug found in
the MAKK2016 import; nothing else has it.)

### Land patterns

| Footprint | Vendor land pattern | Verdict |
|---|---|---|
| `Sensirion_DFN-4_…_SHT4x_NoCentralPad` | Datasheet Figure 10 | ✅ pad size 0.5 × 0.3 mm and 0.8 mm Y pitch match exactly; X placement agrees to ~0.05 mm. **`NoCentralPad` is the correct variant** |
| `WSON-6-1EP_2x2mm_P0.65mm_EP1x1.6mm` (U6, U8) | TI DRV0006B example | ⚠️ 0.65 mm pitch and the 1.0 × 1.6 mm EP match. Pads differ: TI 0.45 × 0.30 at ±0.75 mm, KiCad 0.375 × 0.40 at ±0.887 mm. KiCad's is IPC-7351-derived with a toe fillet; TI's is heel-weighted. Both fully cover the terminal — acceptable, but it is **not** TI's pattern |
| `LGA-14_3x2.5mm_P0.5mm_LayoutBorder3x4y` | **Not in the datasheet** (ST points to st.com/mems) | ⚠️ consistent with the package outline: 3.00 × 2.50 mm body, 0.5 mm pitch, 4/3/4/3 pad arrangement, pads 0.625 × 0.350 vs 0.475 × 0.25 terminals (normal fillet). Pin 1 top-left in top view, matching ST's pin-1 indicator. **Not vendor-land-pattern-verified** |
| `Maxim_OLGA-14_3.3x5.6mm_P0.8mm` | **Not in the datasheet.** It cites "Land Pattern Number 90-0602" at maximintegrated.com | ❌ **still unverified, and this is the $8.34 part.** Pad pitch 0.8 mm and the 7-down-left / 7-up-right arrangement match the pin diagram, but no dimensioned land pattern was available to check pad size or position against |
| `pcb:L_MAKK2016T_2.0x1.6mm` | **No datasheet on file at all** | ❌ still unverified |
| SOT-23 / -23-5 / -23-6, 0402, 0603, D_SMA, TestPoint | KiCad standard IPC-7351 | ✅ correct pad counts and standard numbering; treated as trusted stock geometry, not individually vendor-checked |

### The one decision this audit surfaced — U8 TMP117 thermal pad

`WSON-6-1EP…` gives pad 7 copper **and solder paste**. **[CORRECTED 2026-09-17 — it does not;
the stock footprint has no paste aperture on pad 7. See "U8 TMP117 thermal pad" in the Layout
section, which also records the U6 PowerPAD defect this uncovered.]** The TMP117 symbol has only 6 pins, so
pad 7 carries **no net** — it will be reflowed and left floating.

TI explicitly permits that (*"If the thermal pad is soldered, it must be left floating or
grounded"*), so this is **not an error**. But it is an undocumented choice with a real cost:

- Layout Guidelines: *"To achieve a high precision temperature reading for a rigid PCB, **do not
  solder down the thermal pad**."*
- *"The package thermal pad is not connected to the device ground and should be left unsoldered
  for best measurement accuracy."*
- The headline ±0.1 °C accuracy row in the E-characteristics table is specified **"Thermal Pad
  unsoldered (DRV Package)"**.
- Against that: soldering it *lowers* thermal resistance to the board and *shortens* response
  time; the cost is mechanical stress on the package, which is a measurement-error source unless
  the system is calibrated.

So it is accuracy vs. response time, and it needs a call before layout. If the answer is "do not
solder", the fix is a project copy of the footprint for U8 with pad 7's `F.Paste` removed.
**Note this contradicts the claim in `../parts/V2_BOM.md` that "thermal-pad placement *is* the
measurement" — TI's guidance is the opposite.**

Also note U6 and U8 currently **share one footprint while having opposite exposed-pad
requirements** (the TPS61099 PowerPAD *must* be soldered to GND; the TMP117 pad should not be tied
to device ground). Today that resolves correctly by accident, because only U6's symbol has a pin 7.

### Layout rules this audit extracted

- **SHT40 (U10): "There shall be no copper under the sensor other than at the pin pads."**
  The GND pour needs a keepout under U10 on every layer it would otherwise flood.
- **MAX30101 (U7): the VLED+ bypass capacitor returns to PGND, not GND** (datasheet pin
  description). PGND and GND are one net here, so this is a layout instruction: join them at a
  single point near the part rather than letting LED pulse current share the analog return.

## Open items before this can be frozen

### ~~Three footprints must be created or imported~~ — DONE 2026-09-16

All three now exist in `pcb.pretty/` and the schematic resolves every footprint. ERC footprint
warnings went from 3 to 0.

| Footprint | Source | Verified against |
|---|---|---|
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
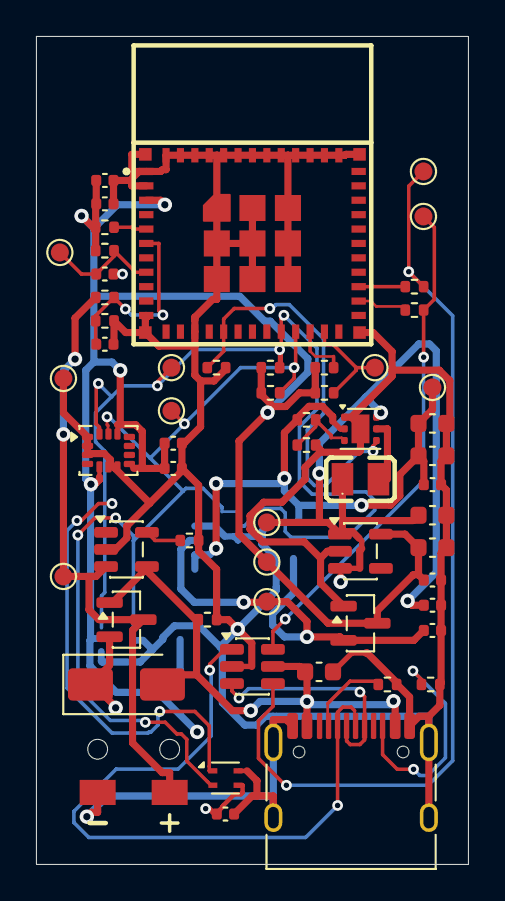
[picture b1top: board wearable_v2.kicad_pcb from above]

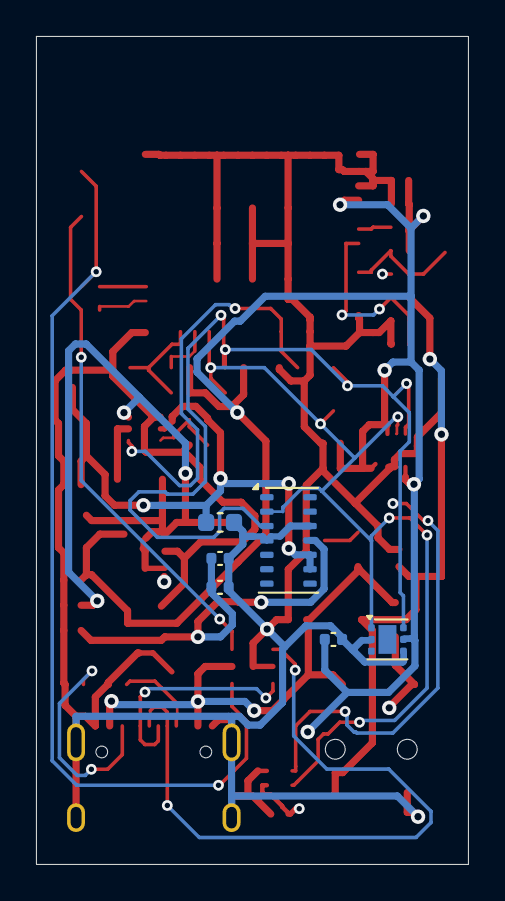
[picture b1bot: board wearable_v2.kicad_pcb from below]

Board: 4 copper layers, 24.0 x 46.0 mm, 64 parts (6 on the bottom side), 26 nets.

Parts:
BT1: LiPo 402030 250mAh; BatteryPads_2x
C1, C15: 4.7uF; C_0603_1608Metric
C2, C12, C13, C16, C17, C18, C19, C20: 100nF; C_0402_1005Metric
C3, C4, C5, C6, C10, C14: 1uF; C_0402_1005Metric
C7, C8, C9, C11: 10uF; C_0603_1608Metric
D1: SS14; D_SMA
J1: TYPE-C-31-M-12; USB_C_Receptacle_HRO_TYPE-C-31-M-12
L1: 2.2uH 1.5A; L_MAKK2016T_2.0x1.6mm
Q1: AO3401A; SOT-23
R1, R2: 5.1k; R_0402_1005Metric
R3, R4: 22R; R_0402_1005Metric
R5, R12, R13, R14, R15: 10k; R_0402_1005Metric
R6, R11: 100k; R_0402_1005Metric
R7, R8, R9: 1M; R_0402_1005Metric
R10: 249k; R_0402_1005Metric
R16, R17: 4.7k; R_0402_1005Metric
TP1: GND; TestPoint_Pad_D1.0mm
TP2: 3V3; TestPoint_Pad_D1.0mm
TP3: 1V8; TestPoint_Pad_D1.0mm
TP4: 4V7; TestPoint_Pad_D1.0mm
TP5: VSYS; TestPoint_Pad_D1.0mm
TP6: BAT+; TestPoint_Pad_D1.0mm
TP7: EN; TestPoint_Pad_D1.0mm
TP8: IO9_BOOT; TestPoint_Pad_D1.0mm
TP9: USB_DM; TestPoint_Pad_D1.0mm
TP10: USB_DP; TestPoint_Pad_D1.0mm
TP11: SDA; TestPoint_Pad_D1.0mm
TP12: SCL; TestPoint_Pad_D1.0mm
U1: ESP32-C3-MINI-1-N4; ESP32-C3-MINI-1
U2: USBLC6-2SC6; SOT-23-6
U3: TP4054-42-SOT25R; SOT-23-5
U4: ME6211C33M5G-N; SOT-23-5
U5: XC6206P182MR; SOT-23
U6: TPS61099DRVR; WSON-6-1EP_2x2mm_P0.65mm_EP1x1.6mm
U7: MAX30101EFD+T; Maxim_OLGA-14_3.3x5.6mm_P0.8mm
U8: TMP117AIDRVR; WSON-6-1EP_2x2mm_P0.65mm_EP1x1.6mm
U9: LSM6DS3TR-C; LGA-14_3x2.5mm_P0.5mm_LayoutBorder3x4y
U10: SHT40-AD1B-R3; Sensirion_DFN-4_1.5x1.5mm_P0.8mm_SHT4x_NoCentralPad

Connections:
1V8: C6.1, C13.1, C14.1, TP3.1 (1_1), U5.2 (VO), U7.11 (VDD)
3V3: C4.1, C5.1, C11.1, C12.1, C17.1, C18.1, C19.1, C20.1, R12.1, R13.1, R14.1, R15.1, R16.1, R17.1, TP2.1 (1_1), U1.3 (3V3), U4.5 (V_{OUT}), U5.3 (VI), U8.5 (V+), U9.5 (VDDIO), U9.8 (VDD), U9.12 (CS), U10.3 (VDD)
4V7: C8.1, C9.1, C15.1, C16.1, R9.1, TP4.1 (1_1), U6.2 (VOUT), U7.9 (VLED+), U7.10 (VLED+)
/BAT_SENSE: C2.1, R7.2, R8.1, U1.6 (IO3)
/CC1: J1.A5 (CC1), R1.1
/CC2: J1.B5 (CC2), R2.1
/EN: C10.1, R12.2, TP7.1 (1_1), U1.8 (EN)
/FB_PPG: R9.2, R10.1, U6.3 (FB)
/IO2_STRAP: R13.2, U1.5 (IO2)
/IO8_STRAP: R14.2, U1.22 (IO8)
/IO9_BOOT: R15.2, TP8.1 (1_1), U1.23 (IO9)
/IO18_USB_DM: R3.1, U1.26 (IO18)
/IO19_USB_DP: R4.1, U1.27 (IO19)
/PPG_PWR_EN: R11.1, U1.16 (IO10), U6.4 (EN)
/PROG: R5.1, U3.5 (PROG)
/SCL: R17.2, TP12.1 (1_1), U1.21 (IO7), U7.2 (SCL), U8.1 (SCL), U9.13 (SCL), U10.2 (SCL)
/SDA: R16.2, TP11.1 (1_1), U1.20 (IO6), U7.3 (SDA), U8.6 (SDA), U9.14 (SDA), U10.1 (SDA)
/SW_PPG: L1.2, U6.5 (SW)
/USB_DM: R3.2, TP9.1 (1_1), U2.6 (I/O1)
/USB_DM_CON: J1.A7 (D-), J1.B7 (D-), U2.1 (I/O1)
/USB_DP: R4.2, TP10.1 (1_1), U2.4 (I/O2)
/USB_DP_CON: J1.A6 (D+), J1.B6 (D+), U2.3 (I/O2)
BAT+: BT1.1 (+), Q1.3 (D), R7.1, TP6.1 (1_1), U3.3 (BAT)
GND: BT1.2 (-), C1.2, C2.2, C3.2, C4.2, C5.2, C6.2, C7.2, C8.2, C9.2, C10.2, C11.2, C12.2, C13.2, C14.2, C15.2, C16.2, C17.2, C18.2, C19.2, C20.2, J1.A1 (GND), J1.A12 (GND), J1.B1 (GND), J1.B12 (GND), J1.SH (SHIELD), R1.2, R2.2, R5.2, R6.2, R8.2, R10.2, R11.2, TP1.1 (1_1), U1.1 (GND), U1.2 (GND), U1.11 (GND), U1.14 (GND), U1.36 (GND), U1.37 (GND), U1.38 (GND), U1.39 (GND), U1.40 (GND), U1.41 (GND), U1.42 (GND), U1.43 (GND), U1.44 (GND), U1.45 (GND), U1.46 (GND), U1.47 (GND), U1.48 (GND), U1.49 (GND), U1.50 (GND), U1.51 (GND), U1.52 (GND), U1.53 (GND), U2.2 (GND), U3.2 (GND), U4.2 (V_{SS}), U5.1 (GND), U6.1 (GND), U6.7 (GND), U7.4 (PGND), U7.12 (GND), U8.2 (GND), U8.4 (ADD0), U9.1 (SDO/SA0), U9.2 (SDX), U9.3 (SCX), U9.6 (GND), U9.7 (GND), U10.4 (VSS)
VBUS: C1.1, D1.2 (A), J1.A4 (VBUS), J1.A9 (VBUS), J1.B4 (VBUS), J1.B9 (VBUS), Q1.1 (G), R6.1, U2.5 (VBUS), U3.4 (VCC)
VSYS: C3.1, C7.1, D1.1 (K), L1.1, Q1.2 (S), TP5.1 (1_1), U4.1 (V_{IN}), U4.3 (CE), U6.6 (VIN)

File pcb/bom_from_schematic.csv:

"Refs","Qty","Value","MPN","LCSC","Footprint"
"C1,C15","2","4.7uF","CL10A475KO8NNNC","C19666","Capacitor_SMD:C_0603_1608Metric"
"C2,C12,C13,C16,C17,C18,C19,C20","8","100nF","CL05B104KO5NNNC","C1525","Capacitor_SMD:C_0402_1005Metric"
"C3,C4,C5,C6,C10,C14","6","1uF","CL05A105KA5NQNC","C52923","Capacitor_SMD:C_0402_1005Metric"
"C7,C8,C9,C11","4","10uF","CL10A106KP8NNNC","C19702","Capacitor_SMD:C_0603_1608Metric"
"D1","1","SS14","SS14","C2480","Diode_SMD:D_SMA"
"J1","1","TYPE-C-31-M-12","TYPE-C-31-M-12","C165948","Connector_USB:USB_C_Receptacle_HRO_TYPE-C-31-M-12"
"L1","1","2.2uH 1.5A","MAKK2016T2R2M","C92923","pcb:L_MAKK2016T_2.0x1.6mm"
"Q1","1","AO3401A","AO3401A","C15127","Package_TO_SOT_SMD:SOT-23"
"R1,R2","2","5.1k","0402WGF5101TCE","C25905","Resistor_SMD:R_0402_1005Metric"
"R3,R4","2","22R","0402WGF220JTCE","C25092","Resistor_SMD:R_0402_1005Metric"
"R5,R12,R13,R14,R15","5","10k","0402WGF1002TCE","C25744","Resistor_SMD:R_0402_1005Metric"
"R6,R11","2","100k","0402WGF1003TCE","C25741","Resistor_SMD:R_0402_1005Metric"
"R7,R8,R9","3","1M","0402WGF1004TCE","C26083","Resistor_SMD:R_0402_1005Metric"
"R10","1","249k","0402WGF2493TCE","C11425","Resistor_SMD:R_0402_1005Metric"
"R16,R17","2","4.7k","0402WGF4701TCE","C25900","Resistor_SMD:R_0402_1005Metric"
"U1","1","ESP32-C3-MINI-1-N4","ESP32-C3-MINI-1-N4","C2838502","pcb:ESP32-C3-MINI-1"
"U2","1","USBLC6-2SC6","USBLC6-2SC6","C7519","Package_TO_SOT_SMD:SOT-23-6"
"U3","1","TP4054-42-SOT25R","TP4054-42-SOT25R","C32574","Package_TO_SOT_SMD:SOT-23-5"
"U4","1","ME6211C33M5G-N","ME6211C33M5G-N","C82942","Package_TO_SOT_SMD:SOT-23-5"
"U5","1","XC6206P182MR","XC6206P182MR","C21659","Package_TO_SOT_SMD:SOT-23"
"U6","1","TPS61099DRVR","TPS61099DRVR","C2842395","Package_SON:WSON-6-1EP_2x2mm_P0.65mm_EP1x1.6mm"
"U7","1","MAX30101EFD+T","MAX30101EFD+T","C2859066","OptoDevice:Maxim_OLGA-14_3.3x5.6mm_P0.8mm"
"U8","1","TMP117AIDRVR","TMP117AIDRVR","C699536","Package_SON:WSON-6-1EP_2x2mm_P0.65mm_EP1x1.6mm"
"U9","1","LSM6DS3TR-C","LSM6DS3TR-C","C967633","Package_LGA:LGA-14_3x2.5mm_P0.5mm_LayoutBorder3x4y"
"U10","1","SHT40-AD1B-R3","SHT40-AD1B-R3","C2848306","Sensor_Humidity:Sensirion_DFN-4_1.5x1.5mm_P0.8mm_SHT4x_NoCentralPad"

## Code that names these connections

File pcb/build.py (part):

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to_rail("J1", "A4", "VBUS", [(7.62, 0), (0, -5.08)])
to_rail("J1", "A1", "GND", [(0, 5.08)])
to_rail("J1", "SH", "GND", [(0, 5.08)])
to_label("J1", "A6", "USB_DP_CON", [(5.08, 0)])
to_label("J1", "B6", "USB_DP_CON", [(5.08, 0)])
to_label("J1", "A7", "USB_DM_CON", [(7.62, 0)])
to_label("J1", "B7", "USB_DM_CON", [(7.62, 0)])
nc("J1", "A8", [(5.08, 0)])
nc("J1", "B8", [(5.08, 0)])
to_label("J1", "A5", "CC1", [(5.08, 0)])
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sch.place("wearable_v2:USBLC6-2SC6", 120, 85, ref="U2", value="USBLC6-2SC6",
          footprint="Package_TO_SOT_SMD:SOT-23-6",
          extra_props=(("LCSC", "C7519"),))
to_label("U2", "1", "USB_DM_CON", [(-5.08, 0)], rot=180)
to_label("U2", "3", "USB_DP_CON", [(-5.08, 0)], rot=180)
to_label("U2", "6", "USB_DM", [(5.08, 0)])
to_label("U2", "4", "USB_DP", [(5.08, 0)])
to_rail("U2", "5", "VBUS", [(0, -5.08)])
to_rail("U2", "2", "GND", [(0, 5.08)])

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to_rail("U3", "4", "VBUS", [(-5.08, 0), (0, -10.16)])
to_rail("U3", "2", "GND", [(0, 5.08)])
to_rail("U3", "3", "BAT+", [(5.08, 0), (0, -5.08)])
to_label("U3", "5", "PROG", [(-7.62, 0)], rot=180)
nc("U3", "1", [(5.08, 0)])

decap("C1", "4.7uF", 175, 48, "VBUS", LC["4u7"], C0603)
pulldown("R5", "10k", 178, 78, LC["10k"], "PROG")

# SS14: USB -> VSYS.  Symbol pin 1 = K (left), pin 2 = A (right).
sch.place("Diode:SS14", 240, 40, ref="D1", value="SS14",
          footprint="Diode_SMD:D_SMA", rot=180,
          extra_props=(("LCSC", "C2480"),))
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to_rail("R7", "1", "BAT+", [(0, -2.54)])
sch.wire(*pin("R7", "2"), *pin("R8", "1"))
sch.junction(*pin("R8", "1"))
sch.label("BAT_SENSE", *pin("R8", "1"))
to_rail("R8", "2", "GND", [(0, 2.54)])
C("C2", "100nF", 192, 114, LC["100n"])
to_label("C2", "1", "BAT_SENSE", [(0, -2.54)])
to_rail("C2", "2", "GND", [(0, 2.54)])

# ============================================================================
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          footprint="Package_SON:WSON-6-1EP_2x2mm_P0.65mm_EP1x1.6mm",
          extra_props=(("LCSC", "C2842395"),))
to_rail("U6", "6", "VSYS", [(-5.08, 0), (0, -7.62)])
to_label("U6", "4", "PPG_PWR_EN", [(-10.16, 0)], rot=180)
to_label("U6", "3", "FB_PPG", [(-10.16, 0)], rot=180)
to_label("U6", "5", "SW_PPG", [(5.08, 0)])
to_rail("U6", "2", "4V7", [(7.62, 0), (0, -7.62)])
to_rail("U6", "1", "GND", [(0, 5.08)])

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          footprint="pcb:L_MAKK2016T_2.0x1.6mm",
          extra_props=(("LCSC", "C92923"),))
to_rail("L1", "1", "VSYS", [(0, -2.54)])
to_label("L1", "2", "SW_PPG", [(0, 2.54)])

decap("C7", "10uF", 463, 58, "VSYS", LC["10u"], C0603)
decap("C8", "10uF", 550, 58, "4V7", LC["10u"], C0603)
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
R("R9", "1M", 480, 88, LC["1M"])
to_rail("R9", "1", "4V7", [(0, -2.54)])
sch.label("FB_PPG", *pin("R9", "2"))
R("R10", "270k", 480, 102, LC["270k"])
to_label("R10", "1", "FB_PPG", [(0, -2.54)])
to_rail("R10", "2", "GND", [(0, 2.54)])
sch.wire(*pin("R9", "2"), *pin("R10", "1"))

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to_rail("U1", "3", "3V3", [(-7.62, 0), (0, -5.08)])
to_rail("U1", "1", "GND", [(0, 7.62)])
to_label("U1", "8", "EN", [(-10.16, 0)], rot=180)
to_label("U1", "5", "IO2_STRAP", [(-12.7, 0)], rot=180)
to_label("U1", "6", "BAT_SENSE", [(-12.7, 0)], rot=180)
for _p in ("12", "13", "18"):
    nc("U1", _p, [(-2.54, 0)])
to_label("U1", "16", "PPG_PWR_EN", [(-12.7, 0)], rot=180)
nc("U1", "19", [(2.54, 0)])
to_label("U1", "20", "SDA", [(7.62, 0)])
to_label("U1", "21", "SCL", [(7.62, 0)])
to_label("U1", "22", "IO8_STRAP", [(7.62, 0)])
to_label("U1", "23", "IO9_BOOT", [(7.62, 0)])
to_label("U1", "26", "IO18_USB_DM", [(7.62, 0)])
to_label("U1", "27", "IO19_USB_DP", [(7.62, 0)])
for _p in ("30", "31"):
    nc("U1", _p, [(2.54, 0)])

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
# USB series resistors, close to the module
R("R3", "22R", 175, 255, LC["22R"])
to_label("R3", "1", "IO18_USB_DM", [(0, -2.54)])
to_label("R3", "2", "USB_DM", [(0, 2.54)])
R("R4", "22R", 200, 255, LC["22R"])
to_label("R4", "1", "IO19_USB_DP", [(0, -2.54)])
to_label("R4", "2", "USB_DP", [(0, 2.54)])

# Shared I2C pull-ups (the bare chips have none; the old breakouts did)
pullup("R16", "4.7k", 40, 275, LC["4k7"], "SDA")
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decap("C20", "100nF", 462, 250, "3V3", LC["100n"])

# ---- PWR_FLAGs -------------------------------------------------------------
# GND, VBUS and VSYS are fed only by passive pins (connector shell, Schottky,
# MOSFET), so ERC needs an explicit power source on each. BAT+ is already
# driven by the TP4054 BAT pin, so it must NOT get a flag as well.
for _i, (_n, _fx) in enumerate([("GND", 500), ("VBUS", 520), ("VSYS", 540)]):
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
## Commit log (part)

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2026-06-21 Project setup
2026-06-21 Remove outdated documentation and add new structured files for development setup, project plan, hardware list, wiring guide, and .gitignore. This update streamlines the project resources for the wear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
2026-06-27 reference images for claude
